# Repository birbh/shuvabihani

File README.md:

# shuvabihani

Shuvabihani is a custom esp32-c3 environmental dashboard and smart alarm clock featuring a WIFI ntp sync with the mx switch inputs and BME680 air quality monitoring. 

## Overview:
Shuvabihani is a Hackclub-BLARE inspired smart alarm clock which introduces ntp time syncing with multi alarm state function. Also this clock measures the environmental state like temperature,humidity and gas resistance and displays the real data in the clock. Also it has some cool smart features like master kill switch that disables all alarms set in the clock. 

### Features:

1. NTP-synced time:
    The clock automatically connects to your home wifi and fetches the precise local time which eliminates the manual clock drift. 

2. Environmental Features:
    It integrates a BME680 sensor to track the temperature, humidity and VOC gas resistance and displays in human readable air quaity ratings. (fresh,fair,poor)

3. Multi alarms:
    The clock supports uoto 5 configurable alarms with onboard UI menu to set hour, min. and active states.

4. Programmed inputs:
    The clock uses the four mx switch in the back very efficiently by using multi button combinations for complex actions like snooze and other normal toggles replacing the need of more buttons and switches.

### Basic clock functions:

The clock uses 4 MX switches for navigation and the alarm control.

- SW1(bottom-left): Up / Increase time
- SW2(bottom-right): Down / Decrease time
- SW3(top-left): Select / Enter Menu
- SW4(bottom-right): Back / Cancel
- Dismiss/Stop Alarm: Press SW1+SW4 simultaneously
- Snooze Alarm(5 mins.): Press SW2+SW3 simultaneously
- Master kill switch: Press SW1+SW4 from the clock screen to disable all alarms.(note: this will work only when you are in clock screen)  

## Hardware assembly and flashing

### 1. Mounting the pcb and components into enclosure:

- Solder the all smd and tht components as required in pcb.
- There are mounting holes in the pcb. So fabricate the pcb and mount them into the base using 4xM3 screws. 
- The front part with display is a bit tricky. You need to mount both the display and the front enclosure into the base using the 2xM2.5 screws at the same time as in the 3Dmodel.
- The front lid is mounted into the base using the 2xM3 screws in the left part and the right part is adjusted automatically with the display mounts.
- And the back part is adjusted by screwing a M3 screws in the middle-top then the 4xM1 screws.
- Then the last part the keycaps are auto adjusted as i have made the different mounting holes for 4 switches which can be inserted as in mechanical keyboard.

### 2. Firmware update and dependencies:

You must install these dependencies in your cpp env. or Arduino ide before flashing the code.
- `Adafruit_GFX`
- `Adafruit_ST7789`
- `Adafruit_BME680`
- `Adafruit_Sensor`
- `WiFi`
- `SPI`
- `Wire`

Also note that you must update your WiFi password and ssid in the firmware before flashing so that the time auto updates fron ntp connecting to your wifi.
code:
``` cpp
    const char* ssid ="insert_ssid_of_wifi";
    const char* password ="insert_password_of_wifi";
```

Also you should update your `gmtOffset_sec` in the code so that it matches with your country's code. For eg: 

``` cpp 
    const long  gmtOffset_sec = 20700; // GMT+5:45 for  Nepal my country(put your country's gmt respectively here)
```

### 3. Flashing the Esp32-c3:
1. Open firmware.ino in the firmware folder in arduino ide.
2. Update the wifi credentials and the timezone gmt in firmware.
3. Select Xiao-esp32c3 as your boarrd.
4. Compile and upload using usb-c.

## How it Works:

The main working principle of the clock is inspired from [Hack Club BLARE](https://blare.hackclub.com/) but i have modified some things and they are:

1. I2C/SPI Pin Constraint:
The standard xiao ESP32-C3 has 11 usable pins. so to support a high res. TFT display, I2C environmental sensor, 4 mechanical switches, and piezo buzzer,a strict pin economy was required. So the display's Reset and Backlight lines are hardwired to the 3.3V power trace and GND respectively on the PCB. This helped two pins (D6 and D8) to be used as  custom I2C bus for the BME680 without dropping any other components.

2. UI change:
The normal clock fails because a delay()  pauses the entire mcu. So shuvabihani uses a non blocking loop and a certain UI states (like CLOCK_VIEW, MENU_SELECT_ALARM, MENU_SET_HOUR, etc.). This thing allows the clock to pulse buzzer, fetch NTP data, read  BME680 , and listen for multi-button  inputs simultaneously without freezing the UI.

## Hardware & Schematic Architecture

- [BLARE Hub KiCad Schematic](https://blare.hackclub.com/docs/pcb-design)
- Display Backlight (BL): Tied to `GND` (Active-LOW enable).
- Display Reset (RST): Tied to `3.3V`.
- I2C Bus: Routed to `D6` (SDA) and `D8` (SCL) for the BME680 sensor.

## Images:
### CAD:
1. Photos:

2. Link:
[FUSION 360](https://a360.co/4z7ZS5Q)

### PCB: 

### Schematic:

## Credits:
- [Hack Club BLARE](https://blare.hackclub.com/): For the hardware inspiration.

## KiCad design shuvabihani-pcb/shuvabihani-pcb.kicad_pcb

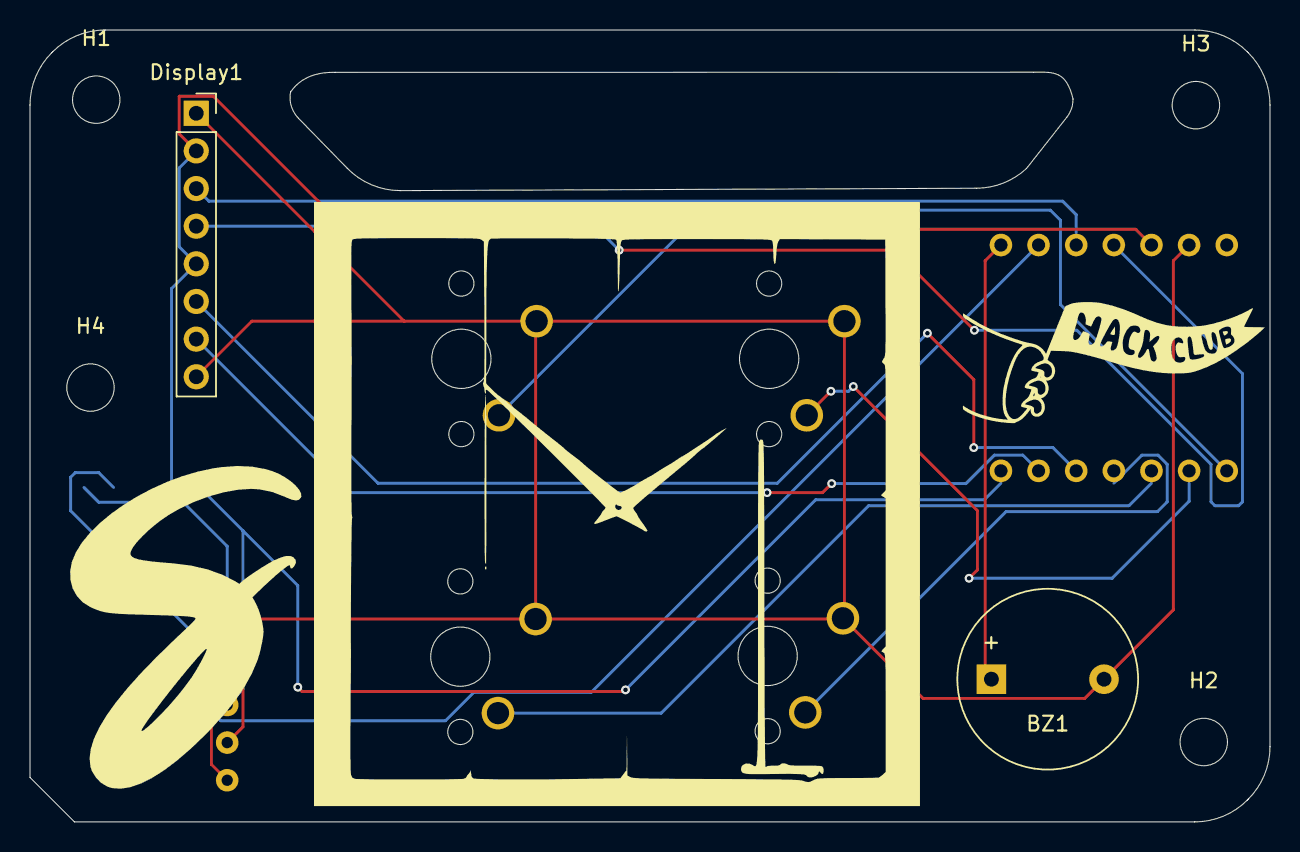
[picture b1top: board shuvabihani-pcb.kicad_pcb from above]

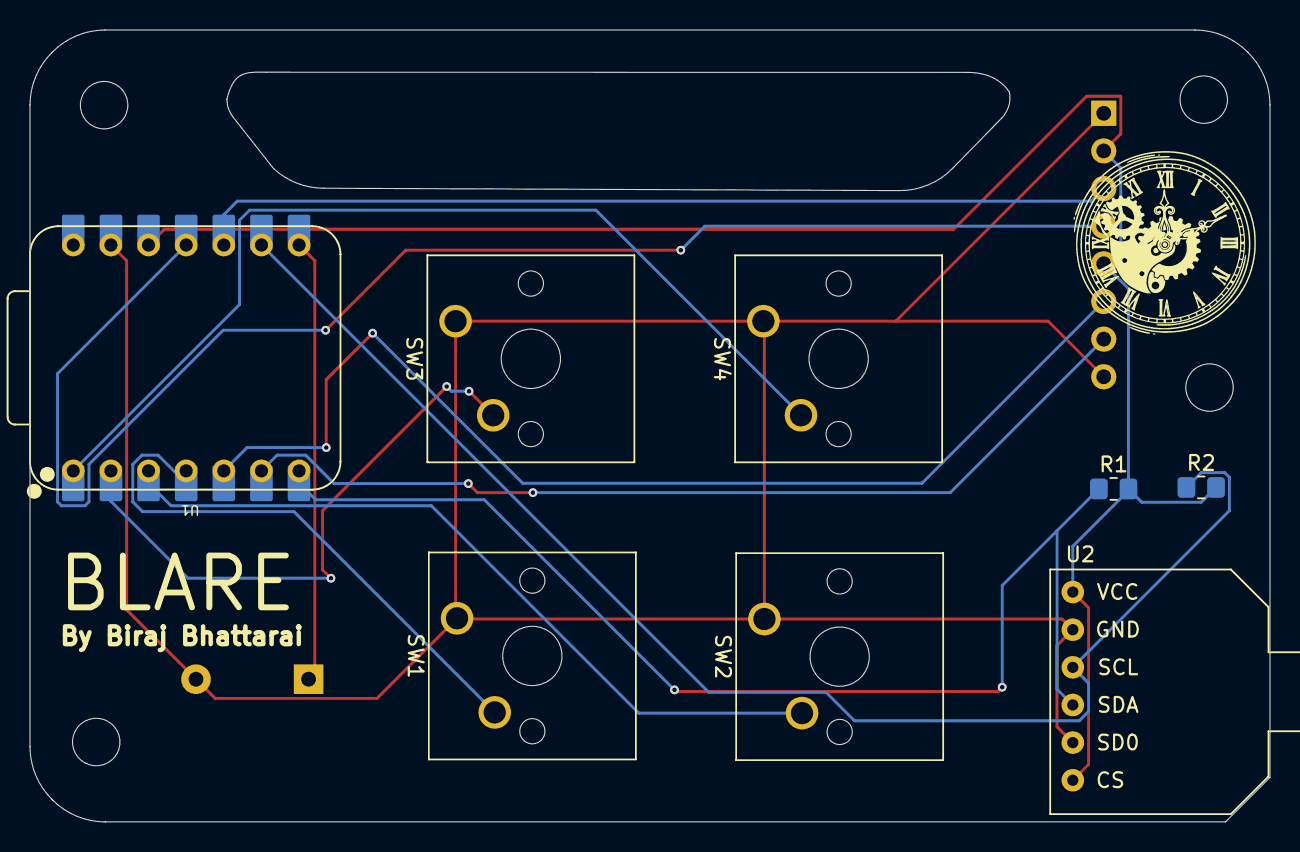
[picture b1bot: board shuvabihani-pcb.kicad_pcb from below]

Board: 2 copper layers, 83.7 x 53.4 mm, 14 parts (8 on the bottom side), 13 nets.

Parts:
BZ1: Buzzer; Buzzer_12x9.5RM7.6
Display1: Conn_01x08_Pin; PinSocket_1x08_P2.54mm_Vertical
H1, H2, H3, H4: MountingHole; MountingHole_3.2mm_M3
R1, R2: 4.7k; R_0805_2012Metric_Pad1.20x1.40mm_HandSolder
SW1, SW2, SW3, SW4: SW_Push; SW_Cherry_MX_1.00u_PCB
U1: XIAO-ESP32-C3-SMD; XIAO-ESP32-C3-DIP
U2: module_bme680

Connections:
3V3: Display1.2, Display1.5, R1.2, R2.2, U1.12 (3V3_OUT), U2.1 (VCC), U2.6 (CS)
/B_SCL: R2.1, U1.9 (D8), U2.3 (SCL)
/B_SDA: R1.1, U1.7 (D6), U2.4 (SDA)
/CS: Display1.7, U1.6 (D5)
/DC: Display1.6, U1.5 (D4)
/SCL: Display1.3, U1.10 (D9/BOOT)
/SDA: Display1.4, U1.11 (D10)
D0: SW4.2, U1.1 (D0)
D1: SW3.2, U1.2 (D1)
D2: SW2.2, U1.3 (D2)
D3: SW1.2, U1.4 (D3)
D7: BZ1.1 (+), U1.8 (D7)
GND: BZ1.2 (-), Display1.1, Display1.8, SW1.1, SW2.1, SW3.1, SW4.1, U1.13 (GND), U2.2 (GND), U2.5 (SD0)

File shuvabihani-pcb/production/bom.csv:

Designator,Footprint,Quantity,Value,LCSC Part #
BZ1,Buzzer_12x9.5RM7.6,1,Buzzer,
DISPLAY1,PinSocket_1x08_P2.54mm_Vertical,1,Conn_01x08_Pin,
"R1, R2",0805,2,4.7k,
"SW1, SW2, SW3, SW4",SW_Cherry_MX_1.00u_PCB,4,SW_Push,
U1,XIAO-ESP32-C3-DIP,1,XIAO-ESP32-C3-SMD,
U2,module_bme680,1,module_bme680,
